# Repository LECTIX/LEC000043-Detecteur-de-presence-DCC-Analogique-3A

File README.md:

# LEC000043-Detecteur-de-presence-DCC-Analogique-3A
Fichiers sources pour le produit LEC000043

## Description du produit

### DCC (Digital)

En DCC, le détecteur d’occupation LEC000043 permet de détecter l’occupation d’un tronçon de voie et de déclencher de nombreux automatismes ou systèmes.
- Détecte tous les trains dans les **2 sens de marche**.
- Seuil de détection **réglable entre 1 et 10 mA**.
- **Courant max supporté** de 3A.
- Temporisation à la désactivation pour **éviter des réactivations intempestives**.
- **Possibilité de forcer** l'activation du relais via un bornier dédié.

### Analogique

Bien que ce module fonctionne en analogique de manière similaire au [LEC000042](https://github.com/LECTIX/LEC000042-Detecteur-de-presence-DCC-Analogique-1A), nous vous conseillons plutôt d'utiliser la version 1A pour une utilisation en analogique.

## Utiliser les fichiers sources pour fabriquer le produit

Il n'est **pas nécessaire de savoir souder ou d'être bon en électronique** pour se procurer ce produit. Grâce aux fichiers sources publiés ici, vous pouvez être en mesure de faire fabriquer ce produit par un sous traitant.

### Faire fabriquer chez un sous traitant

Il est aujourd'hui possible de faire fabriquer à moindre cout des cartes électroniques. Nous recommendons [JLCPCB](https://jlcpcb.com/) si vous voulez aller au moins cher. Si vous préférez un acteur européen, [eurocircuits](https://www.eurocircuits.com/) est un des acteurs reconnus.

1. Télécherger les sources de ce produit en cliquant sur le bouton `Code`, puis `Download ZIP`.
1. Décompresser le dossier.
1. Les fichiers pour la fabrication se trouvent dans le répertoire `hardware/prod`.
1. Se connecter sur [https://cart.jlcpcb.com/quote](https://cart.jlcpcb.com/quote)
1. Cliquer sur le bouton `Add gerber file` et sélectionner le fichier `gerbers.zip`.
1. Sélectionnez la quantité de cartes que vous souhaitez dans le champs `PCB Qty`.
1. Laisser toutes les autres options par défaut, puis cliquez sur le toggle switch en face de `PCB Assembly`, et enfin sur le bouton `confirm`.
1. Une preview de la carte électronique sans les composants doit apparaitre. Cliquez sur `NEXT`.
1. Cliquez sur le bouton `Add BOM File`, puis sélectionnez le fichier `bom.csv`
1. Cliquez sur le bouton `Add CPL File`, puis sélectionnez le fichier `pos.csv`
1. **Vérifier que tous les composants sont en stock** et bien sélectionnés, puis cliquez sur `NEXT`.
1. Une preview de la carte avec ses composants apparait. Continuer le chemin en cliquant sur `NEXT`.
1. Le prix final apparait. Sélectionnez la catégorie du produit, puis cliquez sur `SAVE TO CART`.
1. Une fois sauvegardé dans votre panier, vous pouvez valider votre commande et choisir le moyen d'acheminement. Afin de ne pas avoir à se préoccuper des frais de douane, nous vous conseillons de choisir une méthode d'expédition DDP.

Vous receverez vos cartes sous 1 à 3 semaines. 

**Nous ne sommes en aucun cas responsables des cartes qui arriveraient défectueuses ou non fonctionnelles.**

### Modifications des fichiers sources

Installez kicad 6 (ou version supérieure), et ouvrez le fichier LEC000043.kicad_pro

### Regénérer les fichiers gerber, BOM, et position (Optionnel)

Peut se faire simplement en utilisant kikit :

```
cd hardware
docker run --rm -w /kikit -v $PWD:/kikit yaqwsx/kikit kikit fab jlcpcb --assembly --no-drc --schematic LEC000043.kicad_sch --field LCSC --corrections JLCPCB_CORRECTION --nametemplate LEC000043_{} LEC000043.kicad_pcb prod/

```
## Notices

### DCC

[Manuel FR](docs/dcc/manual_fr.pdf)

[Manuel EN](docs/dcc/manual_en.pdf)

### Analogique

Se référer au produit [LEC000042](https://github.com/LECTIX/LEC000042-Detecteur-de-presence-DCC-Analogique-1A).

## License
Tous nos fichiers sont plubliés sous la license CERN Open Hardware Licence Version 2 - Strongly Reciprocal

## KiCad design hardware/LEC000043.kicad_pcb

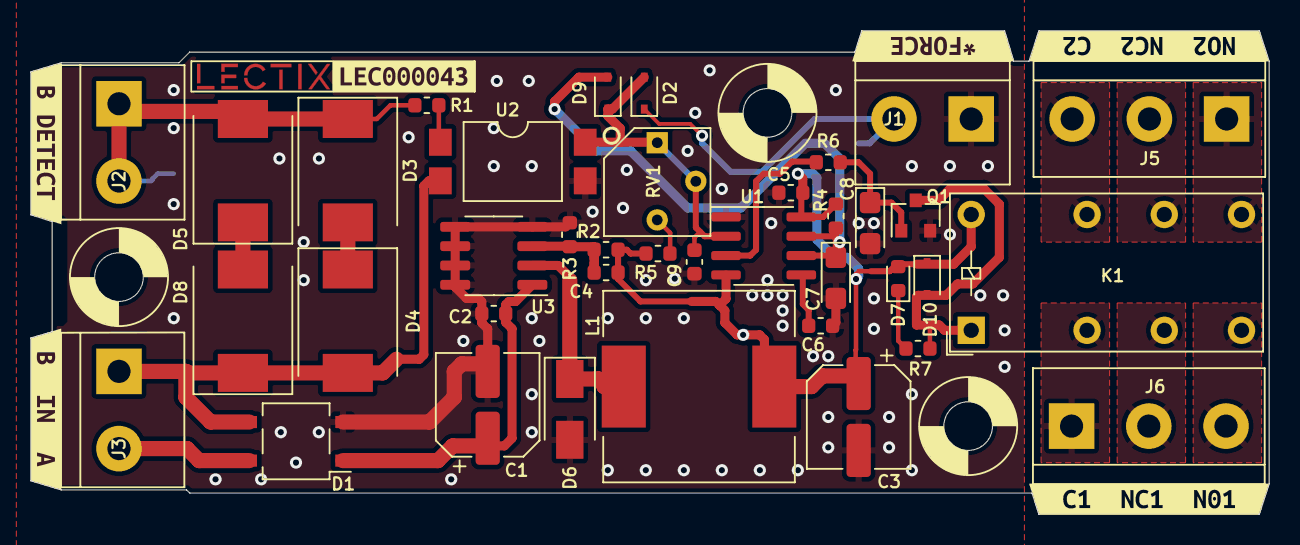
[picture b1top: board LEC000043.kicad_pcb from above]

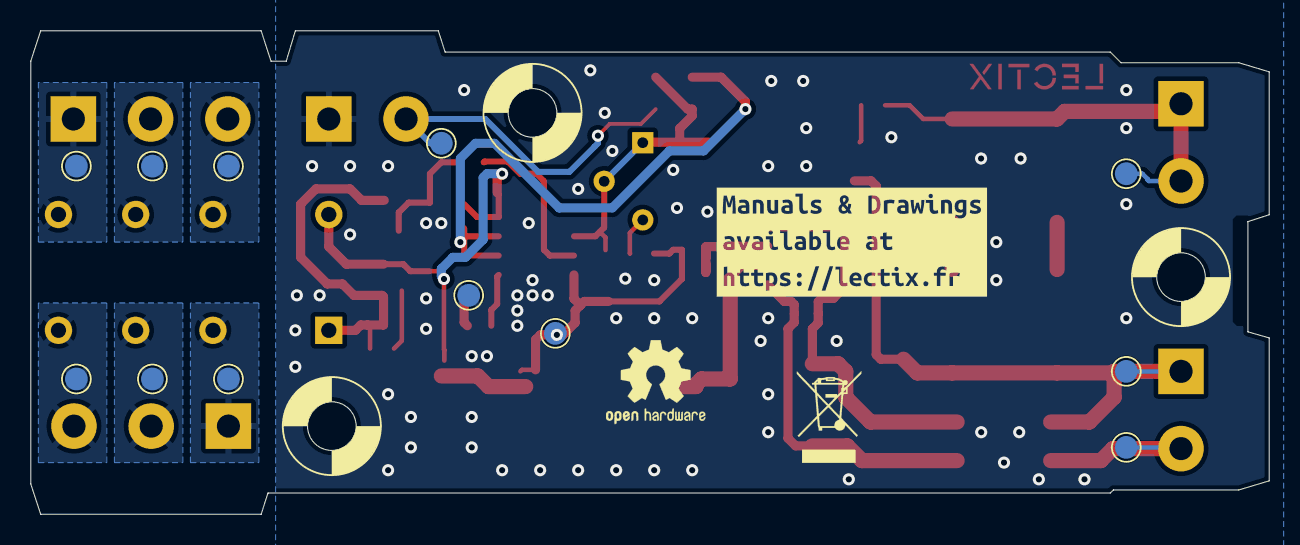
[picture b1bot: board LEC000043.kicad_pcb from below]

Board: 2 copper layers, 81.4 x 31.8 mm, 61 parts (13 on the bottom side), 26 nets.

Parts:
C1, C3: 100uF; CP_Elec_6.3x5.8
C2, C5: 100nF; C_0603_1608Metric
C4, C9: DNP; C_0603_1608Metric
C6: 10n; C_0603_1608Metric
C7, C8: 10uF; CP_EIA-3216-18_Kemet-A
D1: MB10S; TO-269AA
D2, D9, D10: 1N4148WS; D_SOD-323
D3, D4, D5, D8: RS3M; D_SMC
D6: D_Schottky_Small; D_SMA
D7: LED; LED_0603_1608Metric
H1, H2, H3: MountingHole; MountingHole_3.2mm_M3
J1: FORCE_ACTIVATION; TerminalBlock_bornier-2_P5.08mm-blue
J2: TRACKS_OUT; TerminalBlock_bornier-2_P5.08mm-blue
J3: TRACKS_IN; TerminalBlock_bornier-2_P5.08mm-green
J5: CONTACT_1; TerminalBlock_bornier-3_P5.08mm-blue
J6: CONTACT_2; TerminalBlock_bornier-3_P5.08mm-blue
K1: HK19F-5V; Relay_DPDT_HK19F
L1: 47uH; L_12x12mm_H6mm
LOGO1: logo_lectix_25mm; Logo_10mm
Q1: S8050; SOT-23
R1: 27; R_0603_1608Metric
R2: 3k; R_0603_1608Metric
R3, R5, R6: 1k; R_0603_1608Metric
R4: 180k; R_0603_1608Metric
R7: 10k; R_0603_1608Metric
RV1: 500k; BOURNS-3362P_pot
TP1, TP2, TP3, TP4, TP5, TP6, TP7, TP8, TP9, TP10, TP11, TP12: TestPoint_Probe; TestPoint_Pad_D1.5mm
U1: NE555; SOIC-8_3.9x4.9mm_P1.27mm
U2: CYPC817; SMDIP-4_W9.53mm_Clearance8mm
U3: XL1509-ADJE1; SOP-8_3.76x4.96mm_P1.27mm
kibuzzard-624D4A7D: G***; kibuzzard-624D4A7D
kibuzzard-624D4ACF: G***; kibuzzard-624D4ACF
kibuzzard-624D4AF8: G***; kibuzzard-624D4AF8
kibuzzard-624D4BCC: G***; kibuzzard-624D4BCC
kibuzzard-624D4BDE: G***; kibuzzard-624D4BDE
kibuzzard-624D5053: G***; kibuzzard-624D5053
kibuzzard-627C05F6: G***; kibuzzard-627C05F6

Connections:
+5V: C3.1, C4.1, C5.1, D7.2 (A), D10.1 (K), K1.1, L1.1, R2.1, R4.1, R5.1, TP4.1, U1.4 (R), U1.8 (VCC)
/C1: J5.3, K1.4, TP2.1
/C2: J6.1, K1.13, TP11.1
/FORCE: C9.1, D2.2 (A), D9.1 (K), RV1.1, RV1.2, U1.2 (TR), U2.4
/R1: J5.2, K1.6, TP1.1
/R2: J6.2, K1.11, TP5.1
/T1: J5.1, K1.8, TP3.1
/T2: J6.3, K1.9, TP12.1
GND: C1.2, C2.2, C3.2, C5.2, C6.2, C7.2, C8.2, C9.2, D1.2 (-), D6.2 (A), J1.1, Q1.2 (E), R3.2, TP6.1, U1.1 (GND), U2.3, U3.4 (~ENABLE), U3.5 (GND), U3.6 (GND), U3.7 (GND), U3.8 (GND)
unnamed: C1.1, C2.1, D1.1 (+), U3.1 (VIN)
unnamed: C4.2, R2.2, R3.1, U3.3 (FEEDBACK)
unnamed: C6.1, U1.5 (CV)
unnamed: C7.1, D9.2 (A), R4.2, U1.6 (THR), U1.7 (DIS)
unnamed: C8.1, Q1.1 (B), R6.1
unnamed: D3.2 (A), D4.1 (K)
unnamed: D5.1 (K), D8.2 (A)
unnamed: D6.1 (K), L1.2, U3.2 (OUTPUT)
unnamed: D7.1 (K), R7.2
unnamed: D10.2 (A), K1.16, Q1.3 (C), R7.1
unnamed: D2.1 (K), J1.2, TP7.1
unnamed: R1.2, U2.1
unnamed: R5.2, RV1.3
unnamed: R6.2, U1.3 (Q)
TRACK_A: D1.4, J3.2, TP9.1
TRACK_B: D1.3, D4.2 (A), D8.1 (K), J3.1, TP10.1, U2.2
TRACK_B_DETECT_ZONE: D3.1 (K), D5.2 (A), J2.1, J2.2, R1.1, TP8.1

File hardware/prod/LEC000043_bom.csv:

Comment,Designator,Footprint,LCSC
100uF,"C1,C3",0_capacitors:CP_Elec_6.3x5.8,C249982
100nF,"C2,C5",Capacitor_SMD:C_0603_1608Metric,C14663
10n,C6,Capacitor_SMD:C_0603_1608Metric,C57112
10uF,"C7,C8",Capacitor_Tantalum_SMD:CP_EIA-3216-18_Kemet-A,C7171
MB10S,D1,Package_TO_SOT_SMD:TO-269AA,C2488
1N4148WS,"D2,D9,D10",Diode_SMD:D_SOD-323,C2128
RS3M,"D3,D4,D5,D8",Diode_SMD:D_SMC,C330389
D_Schottky_Small,D6,Diode_SMD:D_SMA,C22452
LED,D7,LED_SMD:LED_0603_1608Metric,C72043
FORCE_ACTIVATION,J1,0_connectors:TerminalBlock_bornier-2_P5.08mm-blue,C430621
TRACKS_OUT,J2,0_connectors:TerminalBlock_bornier-2_P5.08mm-blue,C430621
TRACKS_IN,J3,0_connectors:TerminalBlock_bornier-2_P5.08mm-green,C395849
CONTACT_1,J5,0_connectors:TerminalBlock_bornier-3_P5.08mm-blue,C430620
CONTACT_2,J6,0_connectors:TerminalBlock_bornier-3_P5.08mm-blue,C430620
HK19F-5V,K1,0_relays:Relay_DPDT_HK19F,C54512
47uH,L1,Inductor_SMD:L_12x12mm_H6mm,C169398
S8050,Q1,Package_TO_SOT_SMD:SOT-23,C2146
27,R1,Resistor_SMD:R_0603_1608Metric,C25190
3k,R2,Resistor_SMD:R_0603_1608Metric,C4211
1k,"R3,R5,R6",Resistor_SMD:R_0603_1608Metric,C21190
180k,R4,Resistor_SMD:R_0603_1608Metric,C22827
10k,R7,Resistor_SMD:R_0603_1608Metric,C25804
500k,RV1,0_potentiometers:BOURNS-3362P_pot,C125021
NE555,U1,Package_SO:SOIC-8_3.9x4.9mm_P1.27mm,C7593
CYPC817,U2,Package_DIP:SMDIP-4_W9.53mm_Clearance8mm,C385060
XL1509-ADJE1,U3,Package_SO:SOP-8_3.76x4.96mm_P1.27mm,C74192

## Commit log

2023-03-26 Add product manuals
2023-03-26 Add source files
2023-03-26 Add prod files
2023-03-26 Add pdf schematic file
2023-03-26 Add tuto video
